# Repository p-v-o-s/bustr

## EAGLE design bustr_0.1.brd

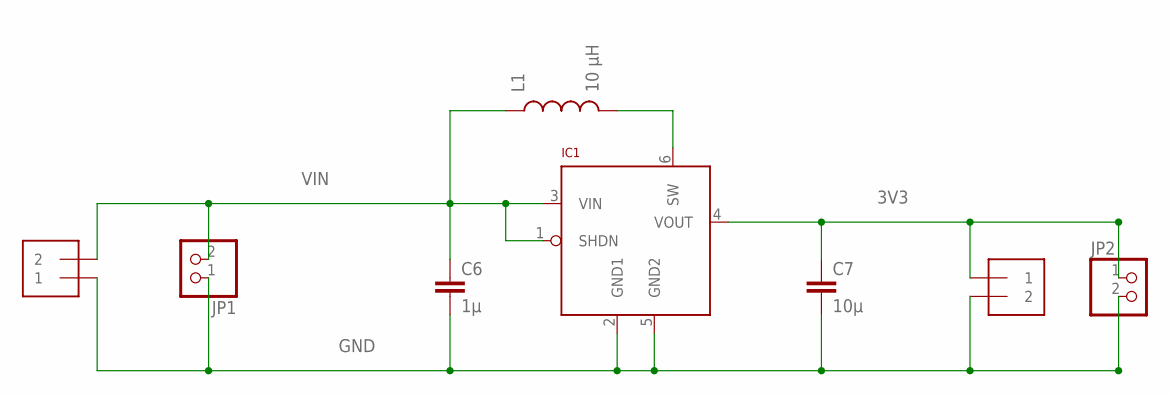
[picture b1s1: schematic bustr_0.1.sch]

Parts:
C6: 1µ; 0603-CAP
C7: 10µ; 0805
IC1: LTC3525; SC70
JP1, JP2: PINHD-1X2; 1X02
L1: 10 µH; 1210
ST1, ST2: 1X2-3.5MM

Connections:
3V3: C7.1, IC1.4 (VOUT), JP2.1, ST2.1
GND: C6.2, C7.2, IC1.2 (GND1), IC1.5 (GND2), JP1.1, JP2.2, ST1.1, ST2.2
unnamed: IC1.6 (SW), L1.2
VIN: C6.1, IC1.1 (SHDN), IC1.3 (VIN), JP1.2, L1.1, ST1.2

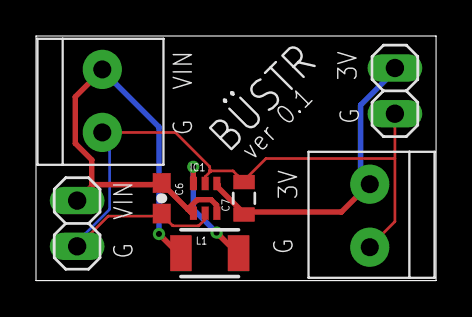
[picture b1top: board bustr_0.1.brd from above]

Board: 2 copper layers, 22.2 x 13.6 mm, 8 parts (0 on the bottom side), 4 nets.

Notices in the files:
bustr_0.1.brd:
CERN OHL v1.2
